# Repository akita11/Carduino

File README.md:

# Carduino

Carduino (v4.1)は、クレジットカードサイズ・厚さ2.4mmの、ArduinoUNO互換機です。
財布などにいつもいれておいて、いつでもその場でArduinoを使うことができます。
「Arduinoは興味あるんだけど、まだ触ったことないんだよね」という人に会ったら、その場でArduinoを体験してもらいましょう。
* ArduinoIDEの導入からLチカまでの手順は、本体裏面にシルクで書かれています。またArduinoIDEのダウンロード先もQRコードで読み取れます。
* USB-Aコネクタ（収納式）で、PCのUSB端子に直接差し込むことができます。またUSB Type-Cケーブルで接続することもできます。
* Arduinoの入出力端子はメスソケットですので、ジャンパワイヤ等をさしてつかうこともできます。
* USB-シリアル変換には、FTDI FT232Rを使っています。
* [スイッチサイエンスで委託販売はじまりました](https://www.switch-science.com/catalog/6368/)

# 使い方

本体裏面のシルクを参照してください。

PCとの接続は、以下の2通りが可能です。
* 本体のコネクタをいったんはずし、以下のようにとりつけ、PCのUSBポートに直接さしこみます。（※コネクタの向きに注意してください。収納時とは表裏を逆にさして使用します。表裏を逆で使用すると、本体やPCを破損する恐れがあります）

* USB Type-Cケーブルを本体コネクタ部にさしこみます。

なお未使用時にUSBコネクタ部を格納しておくコネクタには、A6/A7、電源5V、GNDがつながっています。

# 作り方

* ガーバーデータ(Carduino_v41_gerber.zip)で基板製造（板厚0.6mm）し、部品表（Carduino_v41_bom.xlsx）の部品をとりつけます。
* 4p、6p、8pのピンソケット（各2個：秋月電子等で購入できます）を、基板の溝にあわせて横向けにはんだ付けします。また4pピンヘッダ（秋月電子等で購入できます）をUSBコネクタ側にとりつけます。
* 板厚1mmまたは1.5mmのアクリル板をCarduino_v41_cover.pdfでレーザーカッター等でカットし、本体に透明両面テープや透明ボンド等で固定します。
* ArduinoUNO用のブートローダを書き込みます

# 作者

Junichi Akita (akita@ifdl.jp, @akita11)

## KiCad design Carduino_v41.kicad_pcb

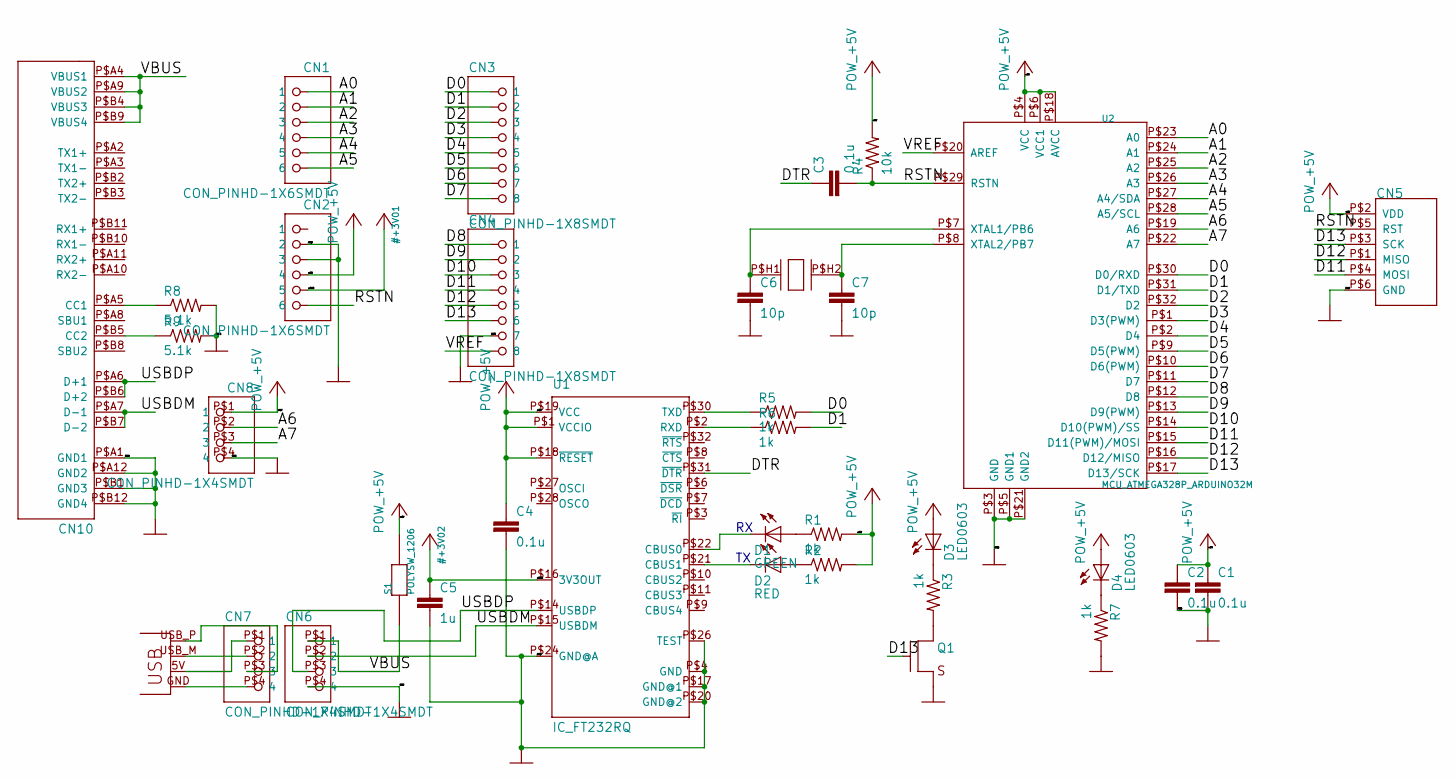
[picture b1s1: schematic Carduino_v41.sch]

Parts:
C1, C2, C3, C4: 0.1u; 0603
C5: 1u; 0603
C6, C7: 10p; 0603
CN1, CN2: CON_PINHD-1X6SMDT; 1X06SMD_THIN
CN3, CN4: CON_PINHD-1X8SMDT; 1X08SMD_THIN
CN5: CON_AVRISPSMD; 2X3SMD
CN6, CN7, CN8: CON_PINHD-1X4SMDT; 1X04SMD_THIN
CN10: CON_USB-CPCBPLUG; USB-C_PCBPLUG
D1: GREEN; SPARKFUN_LED-0603
D2: RED; SPARKFUN_LED-0603
D3, D4: LED0603; SPARKFUN_LED-0603
JP2: CON_USBPCB; USB-A-PCB
Q1: TR_NMOS_IRLML6344; SOT-23-3-2916
R1, R2, R3, R5, R6, R7: 1k; 0603
R4: 10k; 0603
R8, R9: 5.1k; 0603
S1: POLYSW_1206; 1206
U1: IC_FT232RQ; QFN32
U2: MCU_ATMEGA328P_ARDUINO32M; QFN32
X1: XTAL3255; XTAL_3225

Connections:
+3V3: C5.1, CN2.P$5 (5), U1.P$16 (3V3OUT)
+5V: C1.1, C2.1, C4.1, CN2.P$4 (4), CN5.P$2 (VDD), CN8.P$1 (1), D3.A, D4.A, R1.2, R2.2, R4.2, S1.P$2, U1.P$1 (VCCIO), U1.P$18 (~RESET), U1.P$19 (VCC), U2.P$4 (VCC), U2.P$6 (VCC1), U2.P$18 (AVCC)
/A0: CN1.P$1 (1), U2.P$23 (A0)
/A1: CN1.P$2 (2), U2.P$24 (A1)
/A2: CN1.P$3 (3), U2.P$25 (A2)
/A3: CN1.P$4 (4), U2.P$26 (A3)
/A4: CN1.P$5 (5), U2.P$27 (A4/SDA)
/A5: CN1.P$6 (6), U2.P$28 (A5/SCL)
/A6: CN8.P$2 (2), U2.P$19 (A6)
/A7: CN8.P$3 (3), U2.P$22 (A7)
/D0: CN3.P$1 (1), R5.2, U2.P$30 (D0/RXD)
/D1: CN3.P$2 (2), R6.2, U2.P$31 (D1/TXD)
/D2: CN3.P$3 (3), U2.P$32 (D2)
/D3: CN3.P$4 (4), U2.P$1 (D3(PWM))
/D4: CN3.P$5 (5), U2.P$2 (D4)
/D5: CN3.P$6 (6), U2.P$9 (D5(PWM))
/D6: CN3.P$7 (7), U2.P$10 (D6(PWM))
/D7: CN3.P$8 (8), U2.P$11 (D7)
/D8: CN4.P$1 (1), U2.P$12 (D8)
/D9: CN4.P$2 (2), U2.P$13 (D9(PWM))
/D10: CN4.P$3 (3), U2.P$14 (D10(PWM)/SS)
/D11: CN4.P$4 (4), CN5.P$4 (MOSI), U2.P$15 (D11(PWM)/MOSI)
/D12: CN4.P$5 (5), CN5.P$1 (MISO), U2.P$16 (D12/MISO)
/D13: CN4.P$6 (6), CN5.P$3 (SCK), Q1.1 (G), U2.P$17 (D13/SCK)
/DTR: C3.1, U1.P$31 (~DTR)
/RSTN: C3.2, CN2.P$6 (6), CN5.P$5 (RST), R4.1, U2.P$29 (RSTN)
/USBDM: CN6.P$2 (2), CN10.P$A7 (D-1), CN10.P$B7 (D-2), U1.P$15 (USBDM)
/USBDP: CN6.P$3 (3), CN10.P$A6 (D+1), CN10.P$B6 (D+2), U1.P$14 (USBDP)
/VBUS: CN6.P$1 (1), CN10.P$A4 (VBUS1), CN10.P$A9 (VBUS2), CN10.P$B4 (VBUS3), CN10.P$B9 (VBUS4), S1.P$1
/VREF: CN4.P$8 (8), U2.P$20 (AREF)
GND: C1.2, C2.2, C4.2, C5.2, C6.2, C7.2, CN2.P$2 (2), CN2.P$3 (3), CN4.P$7 (7), CN5.P$6 (GND), CN6.P$4 (4), CN8.P$4 (4), CN10.P$A1 (GND1), CN10.P$A12 (GND2), CN10.P$B1 (GND3), CN10.P$B12 (GND4), Q1.2 (S), R7.2, R8.2, R9.2, U1.P$4 (GND), U1.P$17 (GND@1), U1.P$20 (GND@2), U1.P$24 (GND@A), U1.P$26 (TEST), U2.P$3 (GND), U2.P$5 (GND1), U2.P$21 (GND2)
unnamed: C6.1, U2.P$7 (XTAL1/PB6), X1.P$H1
unnamed: C7.1, U2.P$8 (XTAL2/PB7), X1.P$H2
unnamed: CN7.P$1 (1), JP2.5V (VBUS)
unnamed: CN7.P$2 (2), JP2.USB_M (D-)
unnamed: CN7.P$3 (3), JP2.USB_P (D+)
unnamed: CN7.P$4 (4), JP2.GND
unnamed: CN10.P$A5 (CC1), R8.1
unnamed: CN10.P$B5 (CC2), R9.1
unnamed: D1.A, R1.1
unnamed: D1.C, U1.P$22 (CBUS0)
unnamed: D2.A, R2.1
unnamed: D2.C, U1.P$21 (CBUS1)
unnamed: D3.C, R3.1
unnamed: D4.C, R7.1
unnamed: Q1.3 (D), R3.2
unnamed: R5.1, U1.P$30 (TXD)
unnamed: R6.1, U1.P$2 (RXD)

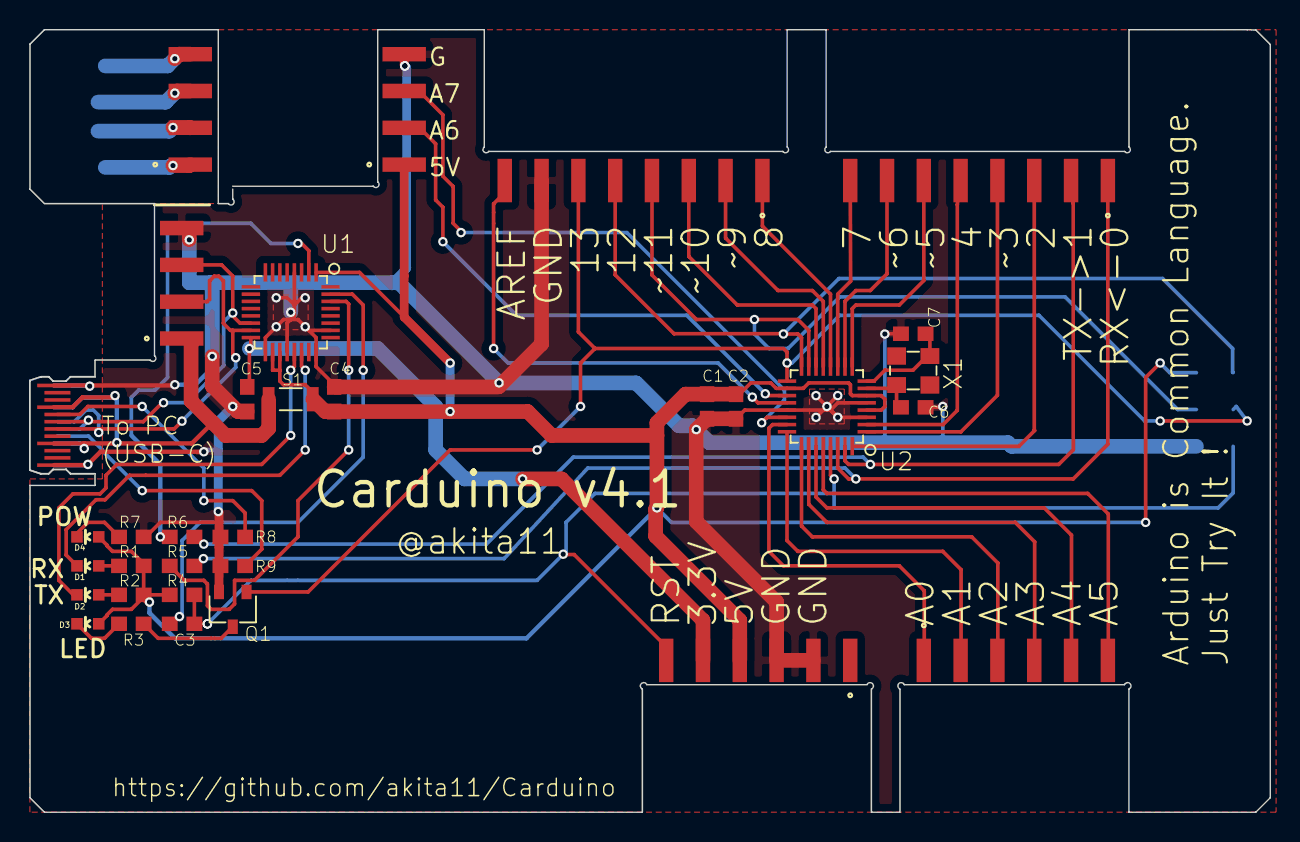
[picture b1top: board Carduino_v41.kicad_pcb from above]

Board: 2 copper layers, 85.6 x 54.0 mm, 35 parts (0 on the bottom side), 48 nets.

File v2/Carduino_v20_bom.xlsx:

BOM for Carduino_v11
Elecrow PN | Parts | Value | Package | QTY | Digikey/Mouser/Manufacturer Part | Remark/ Link
2013010A | C1,C3,C4 | 0.1u | C0603 | 3
2013501A | C2,C5 | 1u | C0603 | 2
4040506A | D1 | Red | D0603 | 1
4040706A | D2,D4 | Green | D0603 | 2
4040606A | D3 | Yellow | D0603 | 1
4021523A | Q1 | CJ2302 | SOT23-3 | 1
1022501A | R1,R2,R3,R5,R6,R7 | 1k | R0603 | 6
1023510A | R4 | 10k | R0603 | 1
4060505A | S1 | PolySW | P1206 | 1
 | U1 | FT232RQ |  | 1 | 68-1008-1-ND | FTDI FT232R, QFN32
 | U2 | ATMEGA328P-MU |  | 1 | ATMEGA328P-MUCT-ND | Microchip ATmega328P, QFN32

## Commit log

2018-06-29 readme.mdを修正
2018-06-29 readme.mdを整理
2018-06-29 readme.mdに画像を追加
2018-06-29 コネクタ部の写真のサイズを縮小
2018-06-29 readme.mdを整形
2018-07-01 readme.mdにA6/A7の情報を追記
2018-07-22 readme.mdに委託販売の情報を追記
2020-05-10 v41データの追加
2020-05-11 写真サイズの修正
2020-05-11 コネクタの表裏についての注意を追記
